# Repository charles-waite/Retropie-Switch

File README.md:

# Raspberry Switch

A handheld, modular, Raspberry Pi-based game console inspired by the Nintendo Switch.  
Designed for RetroPie gaming, open-source hacking, and custom hardware add-ons—housed in a 3D-printed case with real Switch Joycons and tailored for hardware tinkerers.

---

## Table of Contents

- [Project Overview](#project-overview)
- [Features](#features)
- [Hardware List](#hardware-list)
- [Case & Design Notes](#case--design-notes)
- [Joycon Rail Connector](#joycon-rail-connector)
- [To-Do](#to-do)
- [Setup & Install Instructions](#setup--install-instructions)
- [Development Roadmap](#development-roadmap)
- [License](#license)
- [Acknowledgments](#acknowledgments)

---

## Project Overview

**Raspberry Switch** is a DIY handheld gaming console based on the Raspberry Pi 3A+, with a 7" touchscreen, true Joycon compatibility, built-in audio, battery power, and an open 3D-printed enclosure.  
This project aims to be a “Switch-like” device running RetroPie, with modular Python scripts handling hardware functions like backlight, volume, overlay, battery status, and LED indicators.

All hardware and software designs are eventually intended to be open-sourced for others to build, adapt, and contribute.

---

## Features

- RetroPie-based, runs classic games on a handheld Pi
- 3D-printed clamshell case with access panels
- Real Nintendo Switch Joycon rails for detachable controls
- USB-C charging with PiSugar UPS and battery support
- 7” touchscreen display with adjustable backlight (including auto-brightness)
- Custom volume controls (including hardware mute and OSD overlay)
- Stereo amp and speakers (with mini DAC for high-quality audio)
- Headphone jack with auto-mute detection
- On-screen overlays for status and actions
- Status LEDs for power, charging, and battery
- Expandable via internal USB hub for extra controllers/devices
- Open design—schematics, scripts, and CAD files included

---

## Hardware List

- Raspberry Pi 3A+
- PiSugar 3 Plus (battery/UPS)
- 7” Touchscreen display
- Switch Joycon rails (or donor Joycon charger for rails/connector)
- Joycons
- Tiny stereo speakers
- Mini DAC (generic PCM5102A variant)
- Small hardware buttons (power, volume, etc.)
- USB-C charging input relocated/extended from PiSugar
- Liquid flux

---

## Progress pictures

---

## Case & Design Notes

- Custom 3D-printed, clamshell design in two layers (screen bezel, rear case)
- Mounts for all internal components (speakers, amp, DAC, buttons, USB, Joycon rails)
- Foam or adhesive for clean fit to screen
- Mounts directly to LCD panel studs for a robust build

---

## To-Do

- [ ] **Design v1 case** (simple POC, clamshell, access ports)
    - Mounts for speakers, amp, headphone jack, DAC, buttons, USB, Joycon rails, controller board, battery
- [ ] **Integrate buttons** for volume, power, etc.
- [ ] **Upgrade to PiSugar 3 Plus** for power management
- [ ] **Add internal USB hub** (minimum 3 ports: 2 external, 1 internal for Joycons)
- [ ] **Optimize DAC mounting** for durability and space
- [ ] **Setup & test volume/mute buttons**, with auto-mute on headphone insertion
- [ ] **Setup backlight control script**, test with Joycons
- [x] **Create GitHub repo**
- [ ] **Create installer/setup script**
    - [ ] Registers system services at boot
    - [ ] Links scripts and services correctly
    - [ ] Includes update script for pulling changes & restarting services
- [ ] **Refactor scripts** to use Adafruit libraries for reliability
- [ ] **Determine ribbon cable orientation for Joycon rails**
- [x] **Design Joycon Rail cable extender and breakout board variants**
- [ ] **Design custom slider rails using a 4-pin connector to carry VIN/GND + I2C signal**
	- 	Could use a Magnetic "MagSafe" style plug, USB-C plugs, or something like a card edge connector.

---

## Setup & Install Instructions

### 1. Prepare SD Card

- Download and flash the RetroPie IMG to your SD card, or
- Install Raspbian 64-bit Lite (Bookworm) to SD

> **Note for Pi 3/3+:**  
> - Disable WiFi Power Management:  
>   Edit `/etc/rc.local` and add:  
>   ```sh
>   /sbin/iwconfig wlan0 power off
>   exit 0
>   ```
>   Run: `sudo chmod 755 /etc/rc.local`
> - Follow [raspberrypi5-retropie-setup instructions](https://github.com/danielfreer/raspberrypi5-retropie-setup)

### 2. Boot Configuration

- Edit `boot.txt`, comment out `#dtparam=audio=on`
- (Double-check these steps for Bookworm compatibility)

### 3. System Updates

- `sudo apt-get update`
- `sudo apt-get upgrade`
- Boot into RetroPie, run system updates

### 4. Audio & Volume Controls

- Configure virtual sound card for SoftVolume control
- Set up hardware volume/mute buttons and OSD overlay
- Integrate auto-mute on headphone detection (using headphone jack GPIO switch)

### 5. Backlight & Sensor

- Connect and script ambient light sensor to GPIO for auto backlight
- Connect LCD backlight control to GPIO/PWM pin

### 6. Joycon Rails

- Wire rails using Molex ribbon cables per plan above
- Test fit for correct cable orientation and slot routing

### 7. Installer Script (planned)

- Run installer script to set up services and scripts at boot
- Update script for future improvements

---

## Development Roadmap

- Modular Python scripts for backlight, volume, overlay, battery, and status LEDs
- Hardware abstraction to allow swapping components (DAC, screen, battery, etc.)
- Easy-to-follow setup and assembly documentation (including CAD files and images)
- Comprehensive OSD overlay for quick status/config access
- Plug-and-play Joycon integration
- Planned public open-source release when project reaches v1.0

---

## License

*To be added upon public release. Consider using [MIT](https://choosealicense.com/licenses/mit/) or [GPLv3](https://choosealicense.com/licenses/gpl-3.0/) license.*

---

## Acknowledgments

- Inspired by the Nintendo Switch, RetroPie, and countless open-source handheld projects

---

## Contributing

*Contributions, feedback, and hardware test reports are welcome! Please open issues or pull requests once the repo is public.*

---

## Contact

Project lead: charles-waite  
For questions, suggestions, or to get involved, open an issue.

---

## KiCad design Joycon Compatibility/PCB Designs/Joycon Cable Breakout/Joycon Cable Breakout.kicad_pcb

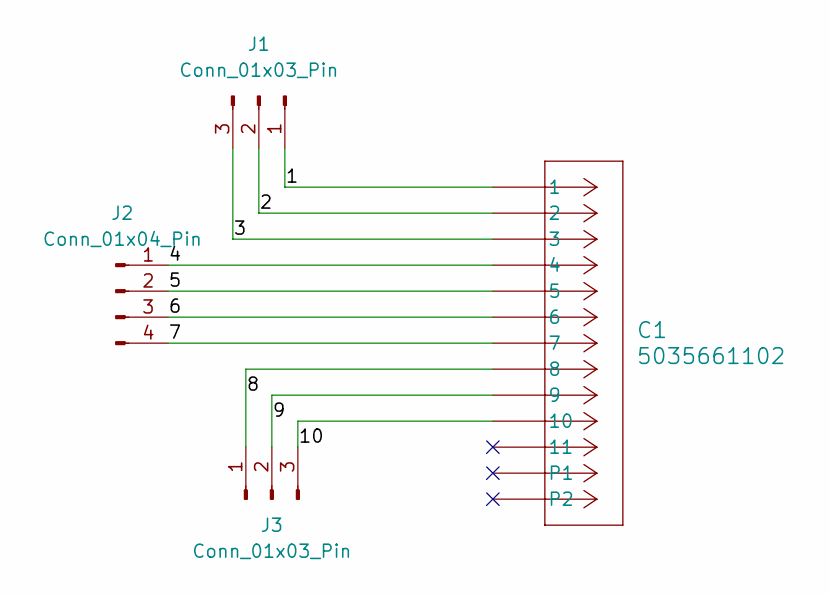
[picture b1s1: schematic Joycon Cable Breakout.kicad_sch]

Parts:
C1: 5035661102; CON_5035661102_MOL
J1, J3: Conn_01x03_Pin; 3-pad-sm
J2: Conn_01x04_Pin; 4-pad-sm-vert

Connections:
/1: C1.1, J1.1
/2: C1.2, J1.2
/3: C1.3, J1.3
/4: C1.4, J2.1
/5: C1.5, J2.2
/6: C1.6, J2.3
/7: C1.7, J2.4
/8: C1.8, J3.1
/9: C1.9, J3.2
/10: C1.10, J3.3

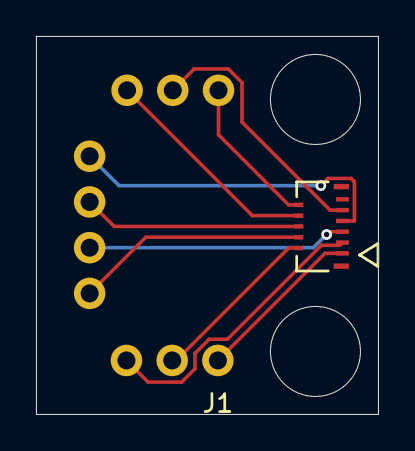
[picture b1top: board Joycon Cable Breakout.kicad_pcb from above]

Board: 2 copper layers, 19.0 x 21.0 mm, 4 parts (0 on the bottom side), 10 nets.

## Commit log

2025-06-22 Initial Commit
    Lots of stuff a WIP, but volume controls mostly tested and functional. Backlight should be functional but untested and needs joycon button mappings.
2025-06-22 Create .gitignore
    Created .gitignore
2025-07-05 Update README.md
    First draft of Readme.md with help from GPT-4.1
2025-07-07 Latest Updates
2025-07-08 Update Ideas and Notes.md
    Added 5mm LED resistor values for equalized percieved brightness.
2025-07-08 Minor update. Testing Sublime Merge functionality.
2025-08-09 Joycon Cable boards and case updates
    Lots of updates. Kicad projects for joycon rail cable extender and breakout. Updated case model with first attempt at making a proper case.
2025-08-11 Added Case Design SVG
2025-08-11 PDf version
2025-08-11 File reorg and resource/diagram additions
2025-08-11 Further organization
2025-08-15 Organization and Fritzing updates
2025-08-18 Added Progress Images
2025-08-18 Fixed readme display
2025-08-18 Still fixing images in readme
2025-08-18 More image fixes
2025-08-18 Image formatting fixed
2025-08-18 Gah!
2025-08-22 Updated Readme, Install instructions, and Gitignore
2025-08-22 Sample MCU scripts added. Haven't tested.
2025-08-28 Create new-main.py
    Revised main.py with event button triggers, smoothing, and clearer documentation.
2025-08-28 Create new-boot.py
    New boot.py method.
2025-10-06 Added Sketches
2026-01-21 Add 7-inch screen STEP model
    Added a new 7-inch Screen STEP file to the hardware models directory for use in mechanical and enclosure design.
